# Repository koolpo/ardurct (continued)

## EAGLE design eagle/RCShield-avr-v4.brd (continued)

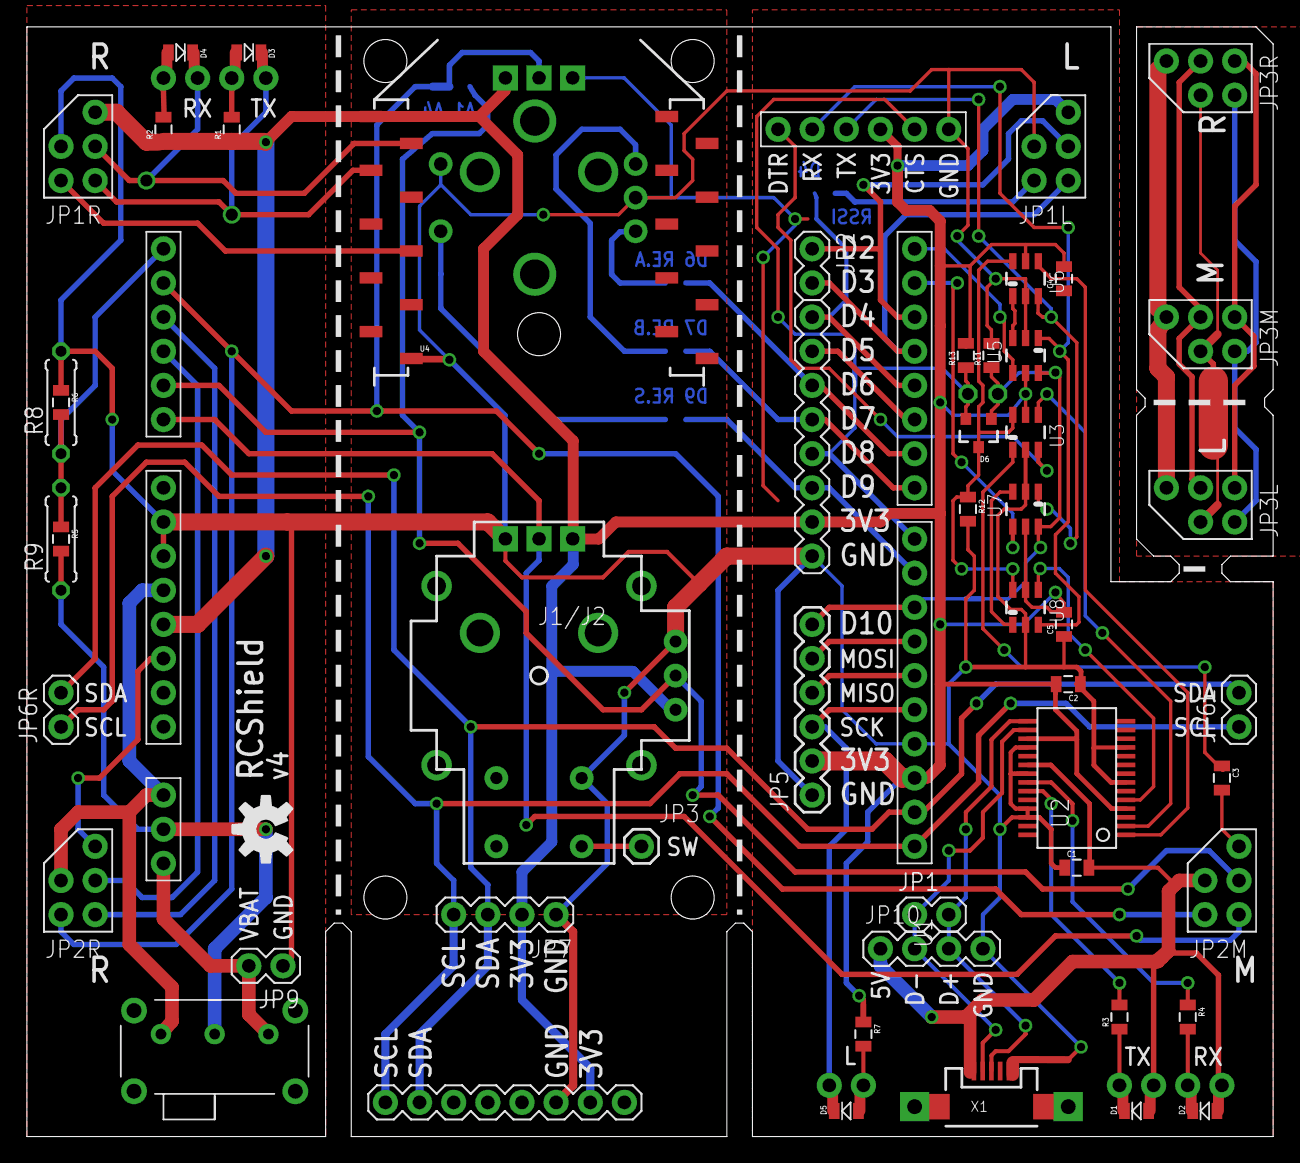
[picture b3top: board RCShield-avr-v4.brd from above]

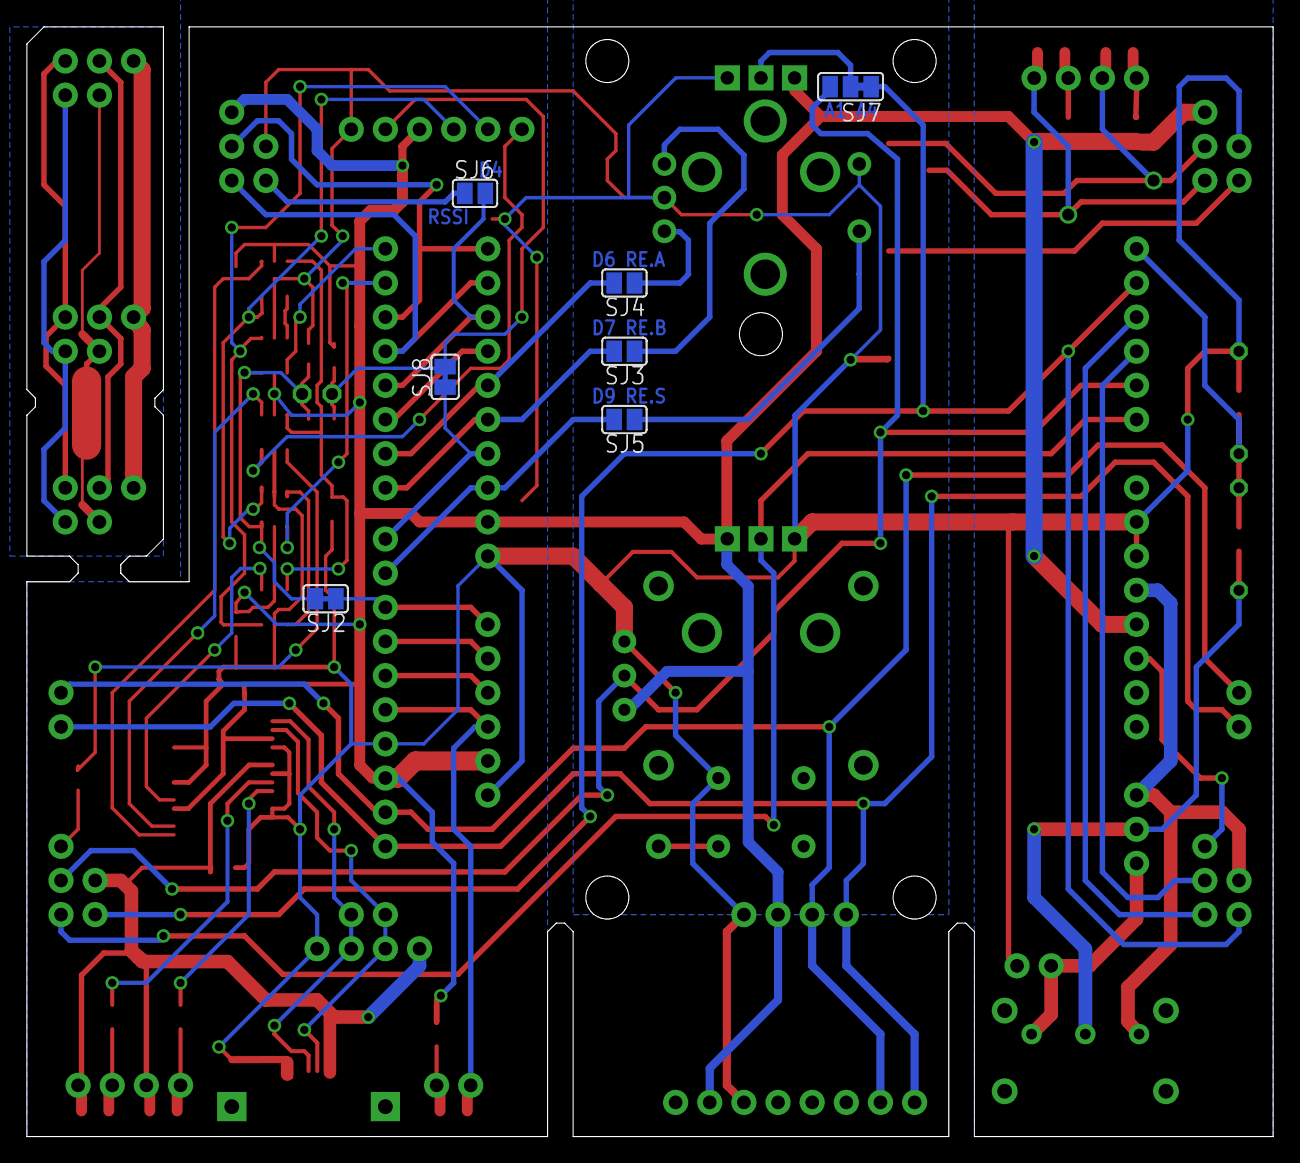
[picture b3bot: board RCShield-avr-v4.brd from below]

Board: 2 copper layers, 92.7 x 82.5 mm, 66 parts (7 on the bottom side), 65 nets.

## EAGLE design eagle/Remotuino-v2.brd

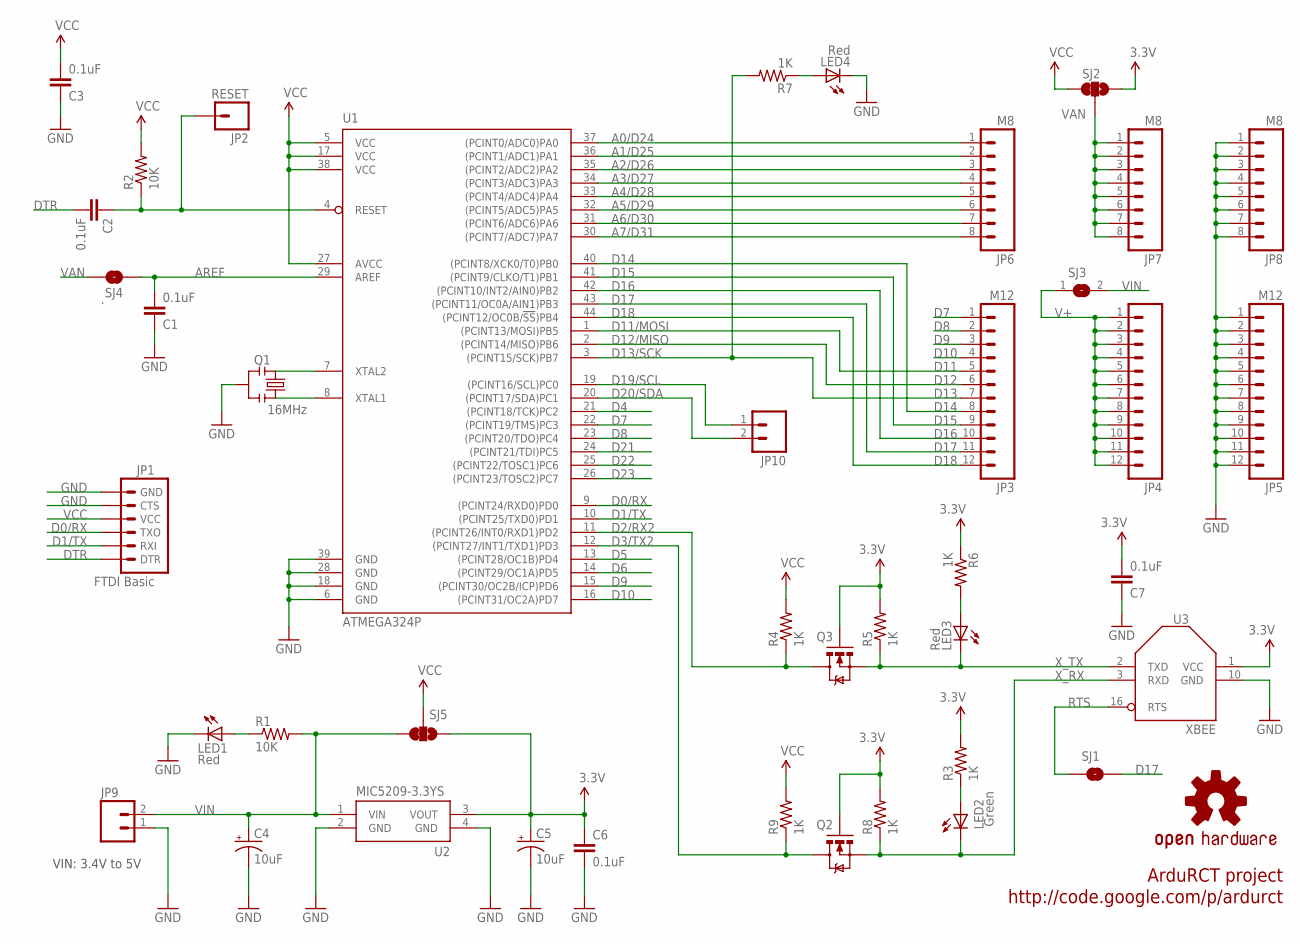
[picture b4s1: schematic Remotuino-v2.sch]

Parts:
C1, C2, C3, C6, C7: 0.1uF; 0805
C4, C5: 10uF; EIA3216
JP1: FTDI Basic; 1X06
JP2: RESET; 1X01
JP3, JP5: M12; 1X12
JP4: M12PTH; 1X12
JP6, JP7, JP8: M8; 1X08
JP9: M02L; 1X2_LONGPAD
JP10: M02; 1X02
LED1, LED3, LED4: Red; LED-0805
LED2: Green; LED-0805
Q1: 16MHz; RESONATOR-SMD
Q2, Q3: BSS138; SOT23-3
R1, R2: 10K; 0805
R3, R4, R5, R6, R7, R8, R9: 1K; 0805
SJ1: SOLDERJUMPERNO; SJ_2S-NO
SJ2, SJ5: SJ_2WAYS_1-2W; SJ_2WAYS_1-2
SJ3: SJ
SJ4: .; SJ_2S-TRACE
U1: ATMEGA324P; TQFP44
U2: MIC5209-3.3YS; SOT223
U3: XBEE; XBEE-MIN
U$2: OSHW-LOGOS; OSHW-LOGO-S

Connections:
3.3V: C5.A (+), C6.1, C7.2, Q2.1 (G), Q3.1 (G), R3.2, R5.2, R6.1, R8.2, SJ2.3, SJ5.3, U2.3 (VOUT), U3.1 (VCC)
A0/D24: JP6.1, U1.37 ((PCINT0/ADC0)PA0)
A1/D25: JP6.2, U1.36 ((PCINT1/ADC1)PA1)
A2/D26: JP6.3, U1.35 ((PCINT2/ADC2)PA2)
A3/D27: JP6.4, U1.34 ((PCINT3/ADC3)PA3)
A4/D28: JP6.5, U1.33 ((PCINT4/ADC4)PA4)
A5/D29: JP6.6, U1.32 ((PCINT5/ADC5)PA5)
A6/D30: JP6.7, U1.31 ((PCINT6/ADC6)PA6)
A7/D31: JP6.8, U1.30 ((PCINT7/ADC7)PA7)
AREF: C1.2, SJ4.2, U1.29 (AREF)
D0/RX: JP1.3 (TXO), U1.9 ((PCINT24/RXD0)PD0)
D1/TX: JP1.2 (RXI), U1.10 ((PCINT25/TXD0)PD1)
D2/RX2: Q3.3 (D), R4.1, U1.11 ((PCINT26/INT0/RXD1)PD2)
D3/TX2: Q2.3 (D), R9.1, U1.12 ((PCINT27/INT1/TXD1)PD3)
D4: U1.21 ((PCINT18/TCK)PC2)
D5: U1.13 ((PCINT28/OC1B)PD4)
D6: U1.14 ((PCINT29/OC1A)PD5)
D7: JP3.1, U1.22 ((PCINT19/TMS)PC3)
D8: JP3.2, U1.23 ((PCINT20/TDO)PC4)
D9: JP3.3, U1.15 ((PCINT30/OC2B/ICP)PD6)
D10: JP3.4, U1.16 ((PCINT31/OC2A)PD7)
D11/MOSI: JP3.5, U1.1 ((PCINT13/MOSI)PB5)
D12/MISO: JP3.6, U1.2 ((PCINT14/MISO)PB6)
D13/SCK: JP3.7, R7.2, U1.3 ((PCINT15/SCK)PB7)
D14: JP3.8, U1.40 ((PCINT8/XCK0/T0)PB0)
D15: JP3.9, U1.41 ((PCINT9/CLKO/T1)PB1)
D16: JP3.10, U1.42 ((PCINT10/INT2/AIN0)PB2)
D17: JP3.11, SJ1.2, U1.43 ((PCINT11/OC0A/AIN1)PB3)
D18: JP3.12, U1.44 ((PCINT12/OC0B/!SS!)PB4)
D19/SCL: JP10.1, U1.19 ((PCINT16/SCL)PC0)
D20/SDA: JP10.2, U1.20 ((PCINT17/SDA)PC1)
D21: U1.24 ((PCINT21/TDI)PC5)
D22: U1.25 ((PCINT22/TOSC1)PC6)
D23: U1.26 ((PCINT23/TOSC2)PC7)
DTR: C2.2, JP1.1 (DTR)
GND: C1.1, C3.1, C4.C (-), C5.C (-), C6.2, C7.1, JP1.5 (CTS), JP1.6 (GND), JP5.1, JP5.2, JP5.3, JP5.4, JP5.5, JP5.6, JP5.7, JP5.8, JP5.9, JP5.10, JP5.11, JP5.12, JP8.1, JP8.2, JP8.3, JP8.4, JP8.5, JP8.6, JP8.7, JP8.8, JP9.1, LED1.2 (C), LED4.2 (C), Q1.2, U1.6 (GND), U1.18 (GND), U1.28 (GND), U1.39 (GND), U2.2 (GND), U2.4 (GND), U3.10 (GND)
unnamed: Q1.1, U1.8 (XTAL1)
unnamed: Q1.3, U1.7 (XTAL2)
unnamed: LED2.1 (A), R3.1
unnamed: LED3.1 (A), R6.2
unnamed: LED4.1 (A), R7.1
unnamed: LED1.1 (A), R1.1
RESET: C2.1, JP2.1, R2.1, U1.4 (RESET)
RTS: SJ1.1, U3.16 (RTS)
V+: JP4.1, JP4.2, JP4.3, JP4.4, JP4.5, JP4.6, JP4.7, JP4.8, JP4.9, JP4.10, JP4.11, JP4.12, SJ3.1
VAN: JP7.1, JP7.2, JP7.3, JP7.4, JP7.5, JP7.6, JP7.7, JP7.8, SJ2.2, SJ4.1
VCC: C3.2, JP1.4 (VCC), R2.2, R4.2, R9.2, SJ2.1, SJ5.2, U1.5 (VCC), U1.17 (VCC), U1.27 (AVCC), U1.38 (VCC)
VIN: C4.A (+), JP9.2, R1.2, SJ3.2, SJ5.1, U2.1 (VIN)
X_RX: LED2.2 (C), Q2.2 (S), R8.1, U3.3 (RXD)
X_TX: LED3.2 (C), Q3.2 (S), R5.1, U3.2 (TXD)

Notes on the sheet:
VIN: 3.4V to 5V
ArduRCT project
http://code.google.com/p/ardurct
D11
D12
D13

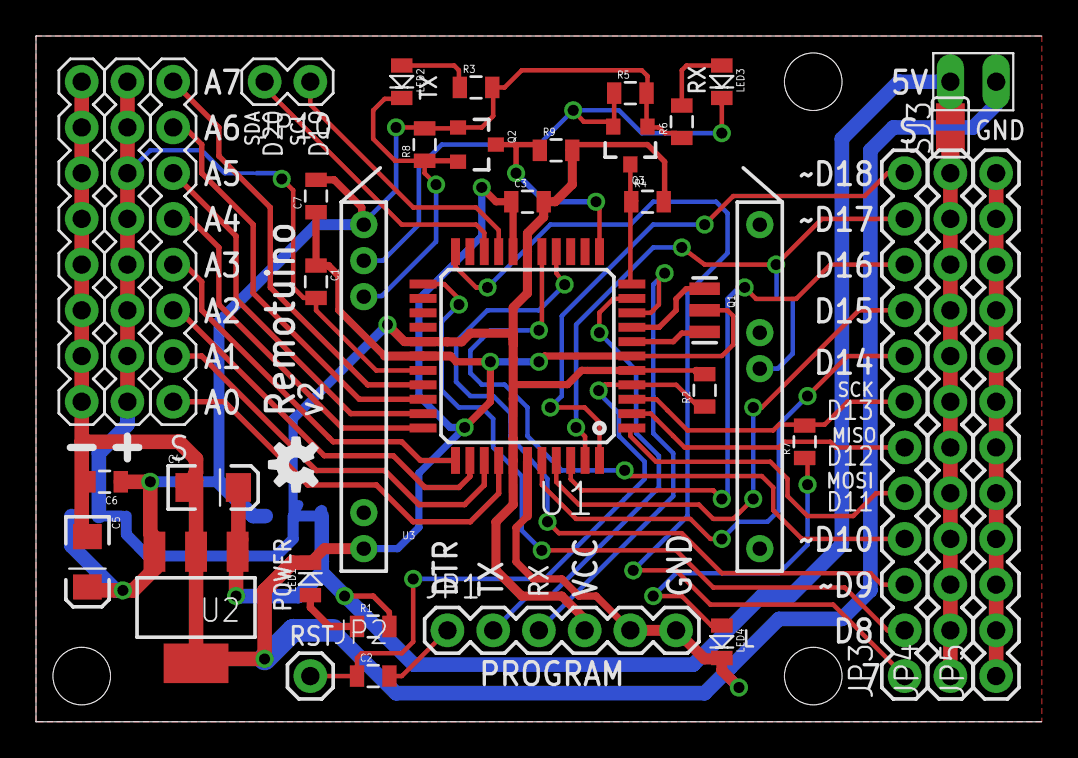
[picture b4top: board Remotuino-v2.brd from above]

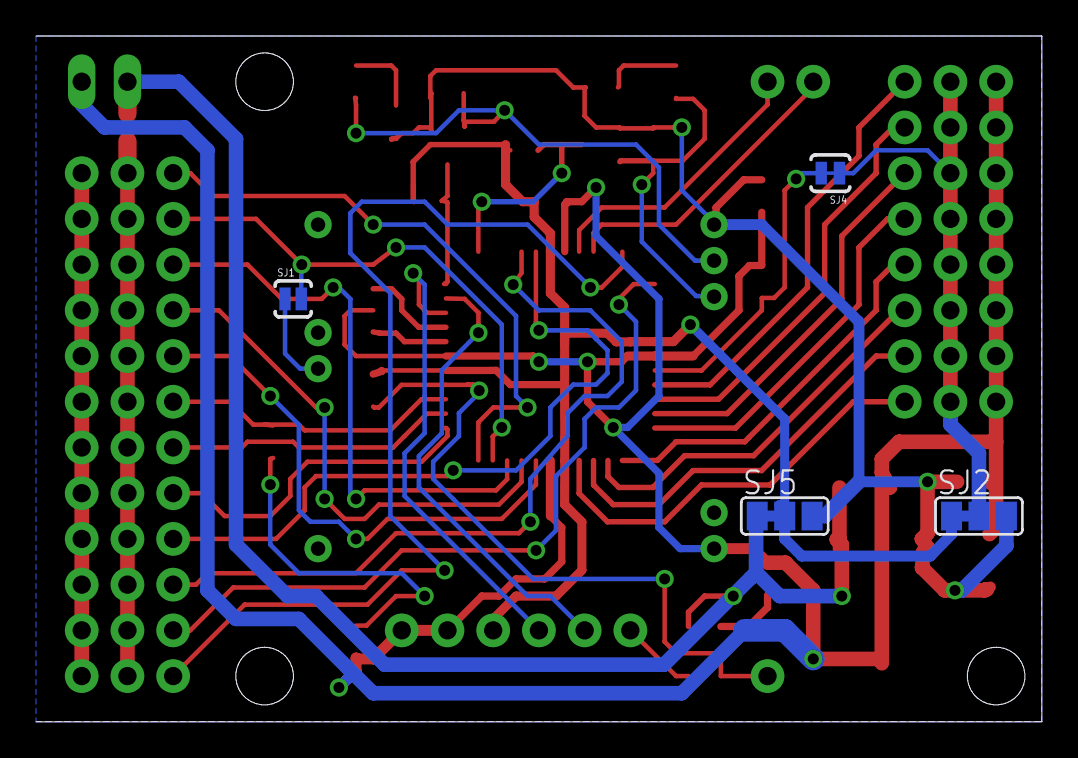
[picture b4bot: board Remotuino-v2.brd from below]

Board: 2 copper layers, 55.9 x 38.1 mm, 42 parts (4 on the bottom side), 44 nets.

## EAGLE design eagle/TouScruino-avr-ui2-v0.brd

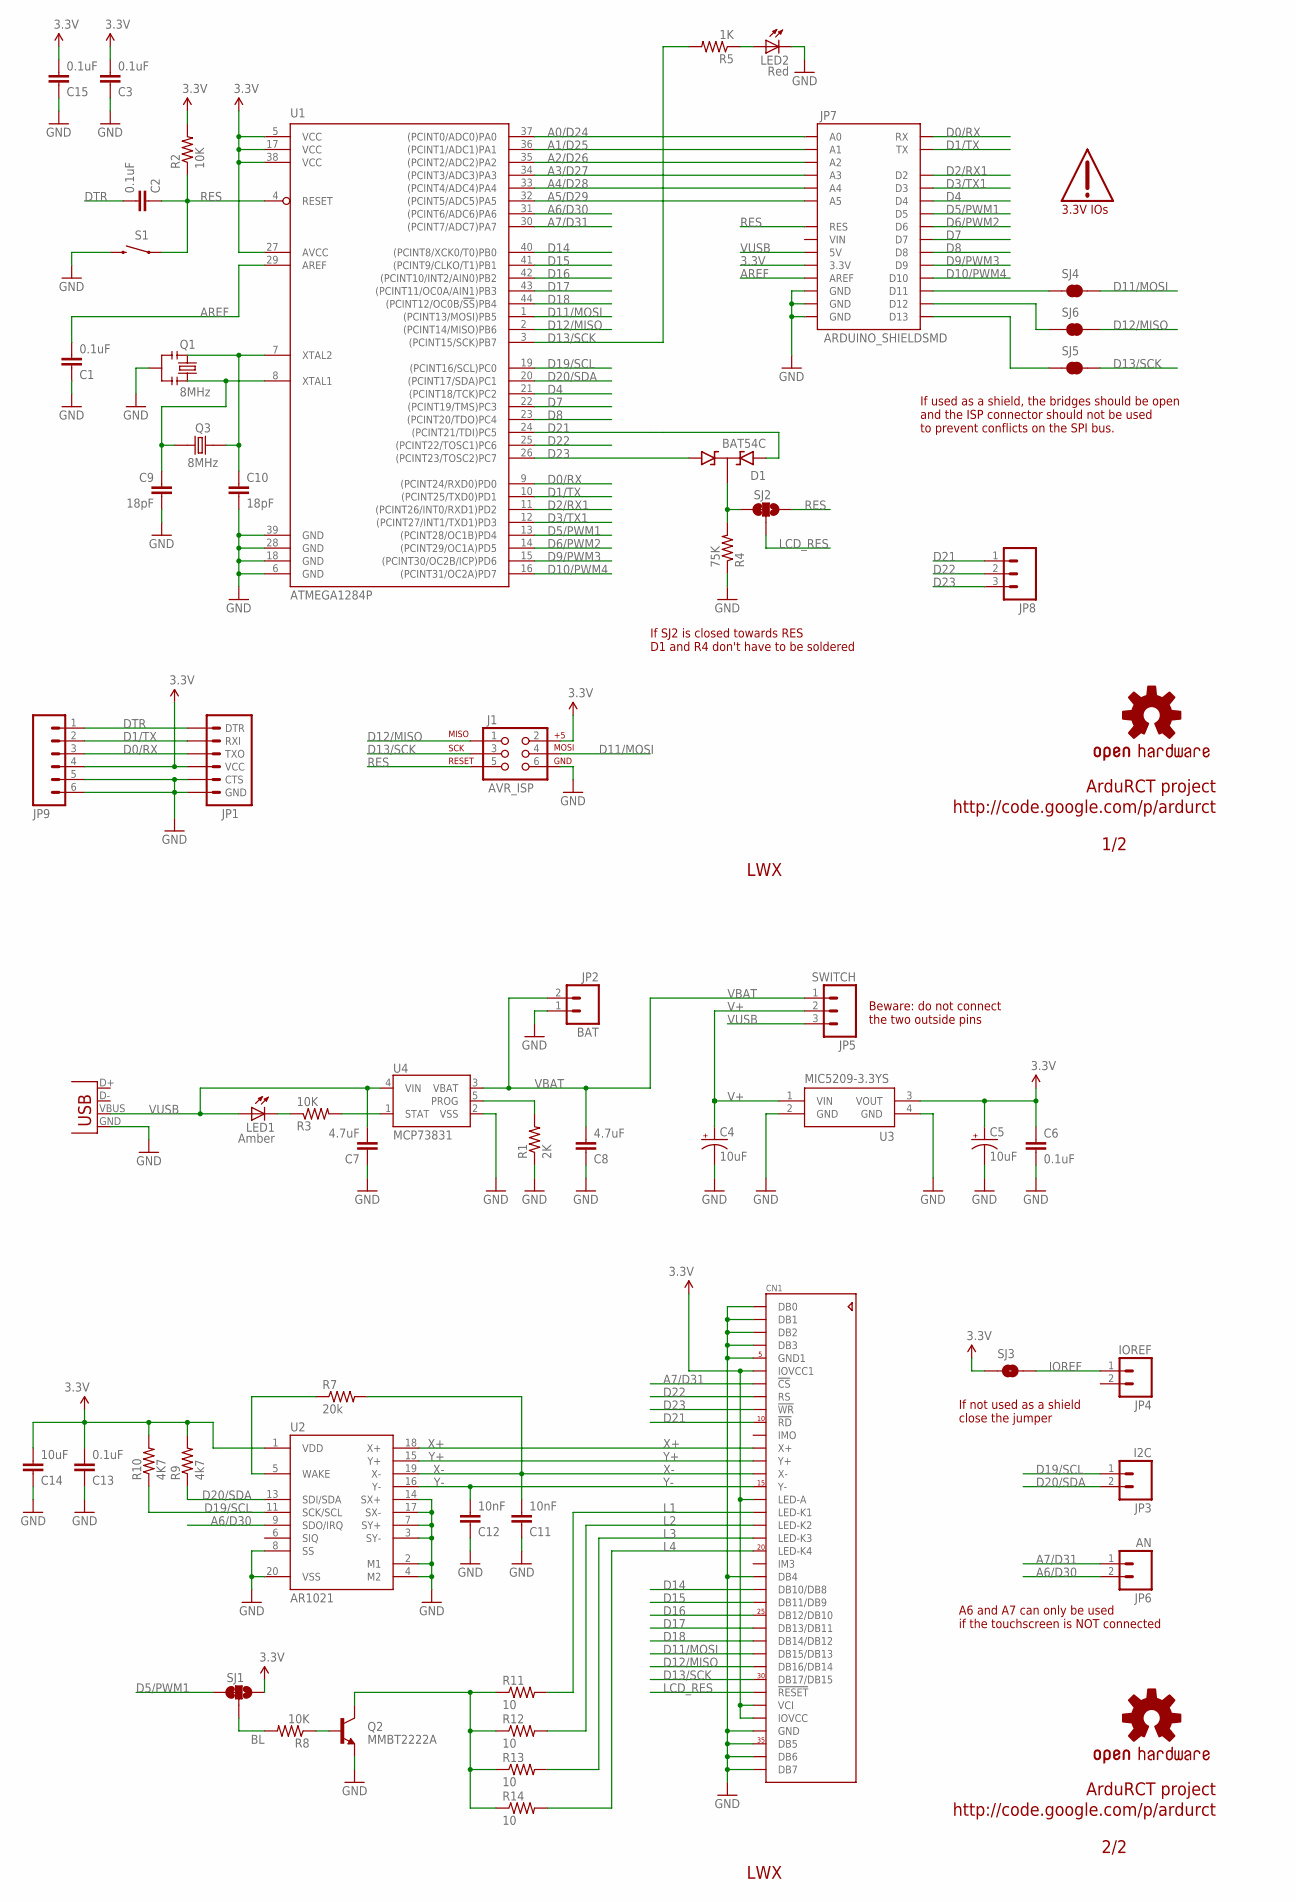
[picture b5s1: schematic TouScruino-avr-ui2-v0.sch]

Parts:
C1, C2, C3, C6, C13, C15: 0.1uF; 0805
C4, C5: 10uF; EIA3216
C7, C8: 4.7uF; 0805
C9, C10: 18pF; 0603-CAP
C11, C12: 10nF; 0805
C14: 10uF; 0805
CN1: ILI9325_LCD1.0MM; ILI9325_28INCH_TS
D1: BAT54C; SOT23-3
J1: AVR_ISP; 2X3
JP1: ARDUINO_SERIAL_PROGRAMPTH; 1X06
JP2: BAT; JST-2-SMD
JP3: I2C; 1X02_SMD
JP4: IOREF; 1X02_SMD
JP5: SWITCH; 1X03_SMD_TH
JP6: AN; 1X02
JP7: ARDUINO_SHIELDSMD; ARDUINO_SHIELD_SMD
JP8: M03PTH; 1X03
JP9: M06SMD; 1X06-SMD
LED1: Amber; LED
LED2: Red; LED
Q1: 8MHz; RESONATOR-SMD
Q2: MMBT2222A; SOT23-3
Q3: 8MHz; CRYSTAL_5X3.2
R1: 2K; 0805
R2, R3, R8: 10K; 0805
R4: 75K; 0805
R5: 1K; 0805
R7: 20k; 0805
R9: 4k7; 0805
R10: 4K7; 0805
R11, R12, R13, R14: 10; 0805
S1: SWITCH-MOMENTARY-2SMD; TACTILE_SWITCH_SMD
SJ1, SJ2: SJ_2WAYS_1-2; SJ_2WAYS_1-2_S
SJ3: SOLDERJUMPERNO; SJ_2S-NO
SJ4, SJ5, SJ6: SOLDERJUMPERTRACE; SJ_2S-TRACE
U1: ATMEGA1284P; TQFP44
U2: AR1021; SSOP20
U3: MIC5209-3.3YS; SOT223
U4: MCP73831; SOT23-5
U$3, U$5: OSHW-LOGOM; OSHW-LOGO-M
U$4: 3.3V_IO
X2: USB; USB-MICROB

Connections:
3.3V: C3.2, C5.A (+), C6.1, C13.2, C14.2, C15.2, CN1.6 (IOVCC1), CN1.16 (LED-A), CN1.32 (VCI), CN1.33 (IOVCC), J1.2, JP1.4 (VCC), JP7.3.3V, JP9.4, R2.2, R9.2, R10.2, SJ1.3, SJ3.1, U1.5 (VCC), U1.17 (VCC), U1.27 (AVCC), U1.38 (VCC), U2.1 (VDD), U3.3 (VOUT)
A0/D24: JP7.A0, U1.37 ((PCINT0/ADC0)PA0)
A1/D25: JP7.A1, U1.36 ((PCINT1/ADC1)PA1)
A2/D26: JP7.A2, U1.35 ((PCINT2/ADC2)PA2)
A3/D27: JP7.A3, U1.34 ((PCINT3/ADC3)PA3)
A4/D28: JP7.A4, U1.33 ((PCINT4/ADC4)PA4)
A5/D29: JP7.A5, U1.32 ((PCINT5/ADC5)PA5)
A6/D30: JP6.2, U1.31 ((PCINT6/ADC6)PA6), U2.9 (SDO/IRQ)
A7/D31: CN1.7 (!CS), JP6.1, U1.30 ((PCINT7/ADC7)PA7)
AREF: C1.2, JP7.AREF, U1.29 (AREF)
BL: R8.2, SJ1.2
D0/RX: JP1.3 (TXO), JP7.RX, JP9.3, U1.9 ((PCINT24/RXD0)PD0)
D1/TX: JP1.2 (RXI), JP7.TX, JP9.2, U1.10 ((PCINT25/TXD0)PD1)
D2/RX1: JP7.D2, U1.11 ((PCINT26/INT0/RXD1)PD2)
D3/TX1: JP7.D3, U1.12 ((PCINT27/INT1/TXD1)PD3)
D4: JP7.D4, U1.21 ((PCINT18/TCK)PC2)
D5/PWM1: JP7.D5, SJ1.1, U1.13 ((PCINT28/OC1B)PD4)
D6/PWM2: JP7.D6, U1.14 ((PCINT29/OC1A)PD5)
D7: JP7.D7, U1.22 ((PCINT19/TMS)PC3)
D8: JP7.D8, U1.23 ((PCINT20/TDO)PC4)
D9/PWM3: JP7.D9, U1.15 ((PCINT30/OC2B/ICP)PD6)
D10/PWM4: JP7.D10, U1.16 ((PCINT31/OC2A)PD7)
D11/MOSI: CN1.28 (DB15/DB13), J1.4, SJ4.2, U1.1 ((PCINT13/MOSI)PB5)
D12/MISO: CN1.29 (DB16/DB14), J1.1, SJ6.2, U1.2 ((PCINT14/MISO)PB6)
D13/SCK: CN1.30 (DB17/DB15), J1.3, R5.2, SJ5.2, U1.3 ((PCINT15/SCK)PB7)
D14: CN1.23 (DB10/DB8), U1.40 ((PCINT8/XCK0/T0)PB0)
D15: CN1.24 (DB11/DB9), U1.41 ((PCINT9/CLKO/T1)PB1)
D16: CN1.25 (DB12/DB10), U1.42 ((PCINT10/INT2/AIN0)PB2)
D17: CN1.26 (DB13/DB11), U1.43 ((PCINT11/OC0A/AIN1)PB3)
D18: CN1.27 (DB14/DB12), U1.44 ((PCINT12/OC0B/!SS!)PB4)
D19/SCL: JP3.1, R10.1, U1.19 ((PCINT16/SCL)PC0), U2.11 (SCK/SCL)
D20/SDA: JP3.2, R9.1, U1.20 ((PCINT17/SDA)PC1), U2.13 (SDI/SDA)
D21: CN1.10 (!RD), D1.2 (A2), JP8.1, U1.24 ((PCINT21/TDI)PC5)
D22: CN1.8 (RS), JP8.2, U1.25 ((PCINT22/TOSC1)PC6)
D23: CN1.9 (!WR), D1.1 (A1), JP8.3, U1.26 ((PCINT23/TOSC2)PC7)
DTR: C2.2, JP1.1 (DTR), JP9.1
GND: C1.1, C3.1, C4.C (-), C5.C (-), C6.2, C7.1, C8.1, C9.2, C10.2, C11.1, C12.1, C13.1, C14.1, C15.1, CN1.1 (DB0), CN1.2 (DB1), CN1.3 (DB2), CN1.4 (DB3), CN1.5 (GND1), CN1.22 (DB4), CN1.34 (GND), CN1.35 (DB5), CN1.36 (DB6), CN1.37 (DB7), J1.6, JP1.5 (CTS), JP1.6 (GND), JP2.1, JP7.GND@0 (GND), JP7.GND@1 (GND), JP7.GND@2 (GND), JP9.5, JP9.6, LED2.C1 (C), Q1.2, Q2.2 (E), R1.1, R4.1, S1.3 (2), U1.6 (GND), U1.18 (GND), U1.28 (GND), U1.39 (GND), U2.2 (M1), U2.3 (SY-), U2.4 (M2), U2.7 (SY+), U2.8 (SS), U2.14 (SX+), U2.17 (SX-), U2.20 (VSS), U3.2 (GND), U3.4 (GND), U4.2 (VSS), X2.GND
IOREF: JP4.1, SJ3.2
L1: CN1.17 (LED-K1), R11.2
L2: CN1.18 (LED-K2), R12.2
L3: CN1.19 (LED-K3), R13.2
L4: CN1.20 (LED-K4), R14.2
LCD_RES: CN1.31 (!RESET), SJ2.2
unnamed: C9.1, Q1.1, Q3.2, U1.8 (XTAL1)
unnamed: C10.1, Q1.3, Q3.1, U1.7 (XTAL2)
unnamed: JP7.D11, SJ4.1
unnamed: Q2.1 (B), R8.1
unnamed: LED2.A1 (A), R5.1
unnamed: R7.1, U2.5 (WAKE)
unnamed: Q2.3 (C), R11.1, R12.1, R13.1, R14.1
unnamed: LED1.C1 (C), R3.1
unnamed: D1.3 (K), R4.2, SJ2.1
unnamed: JP7.D13, SJ5.1
unnamed: R3.2, U4.1 (STAT)
unnamed: R1.2, U4.5 (PROG)
unnamed: JP7.D12, SJ6.1
RES: C2.1, J1.5, JP7.RES, R2.1, S1.1, SJ2.3, U1.4 (RESET)
V+: C4.A (+), JP5.2, U3.1 (VIN)
VBAT: C8.2, JP2.2, JP5.1, U4.3 (VBAT)
VUSB: C7.2, JP5.3, JP7.5V, LED1.A1 (A), U4.4 (VIN), X2.VBUS
X+: CN1.12 (X+), U2.18 (X+)
X-: C11.2, CN1.14 (X-), R7.2, U2.19 (X-)
Y+: CN1.13 (Y+), U2.15 (Y+)
Y-: C12.2, CN1.15 (Y-), U2.16 (Y-)

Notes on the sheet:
LWX
1/2
2/2
Beware: do not connect the two outside pins
If not used as a shield close the jumper
ArduRCT project
http://code.google.com/p/ardurct
If used as a shield, the bridges should be open and the ISP connector should not be used to prevent conflicts on the SPI bus.
A6 and A7 can only be used if the touchscreen is NOT connected
If SJ2 is closed towards RES D1 and R4 don't have to be soldered

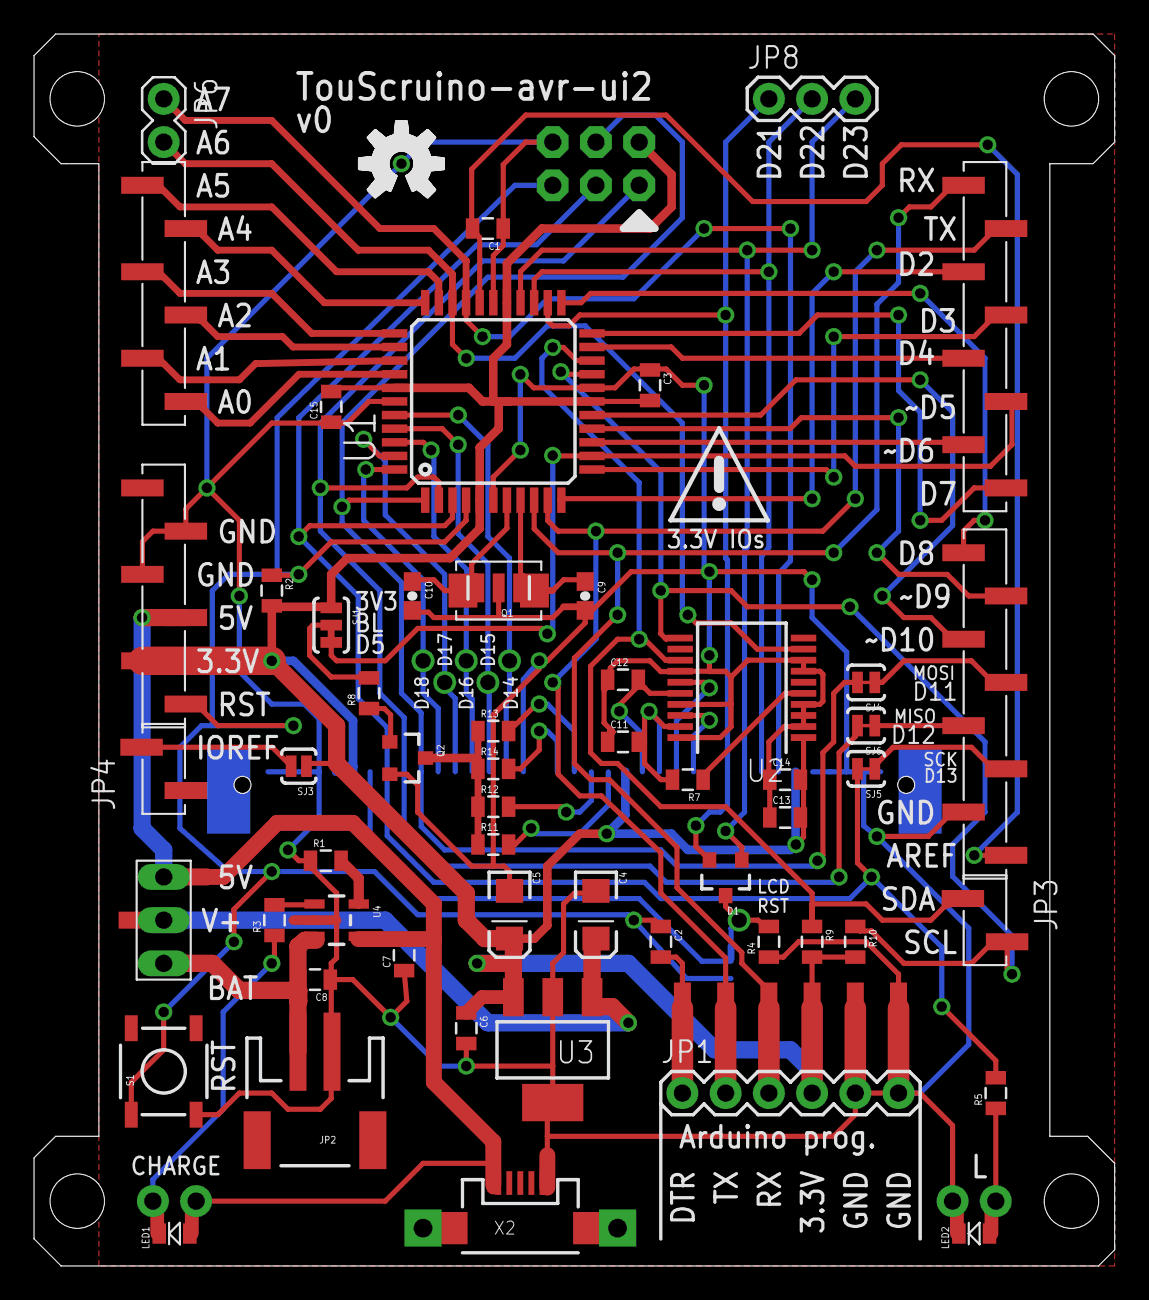
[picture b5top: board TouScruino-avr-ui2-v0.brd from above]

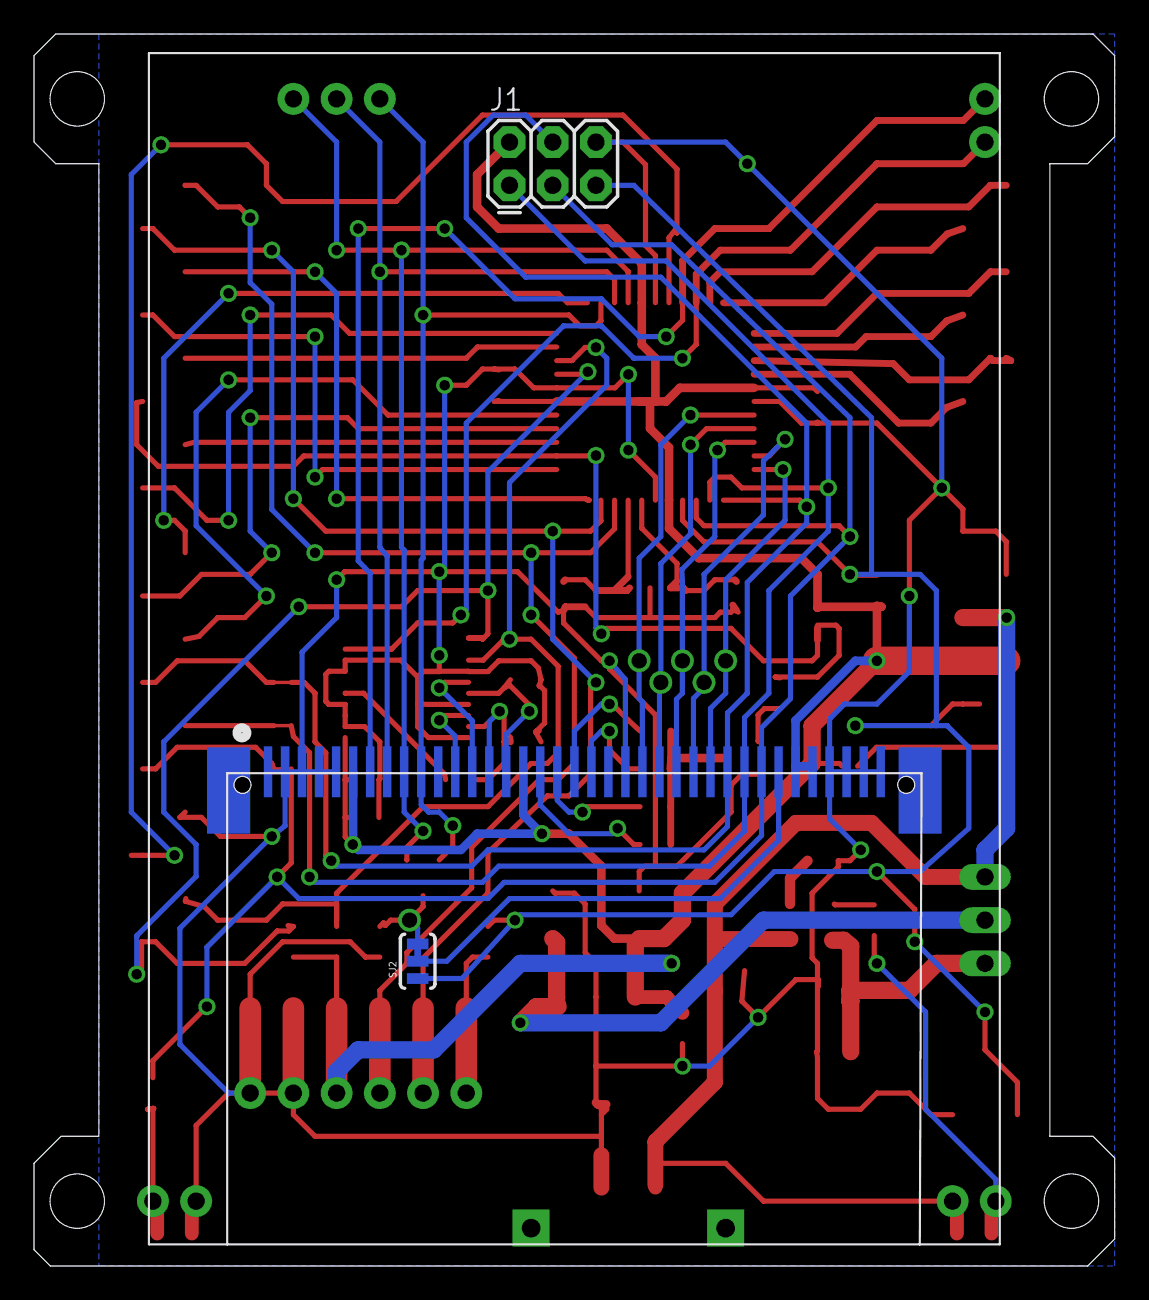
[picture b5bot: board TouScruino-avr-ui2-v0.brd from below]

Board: 2 copper layers, 63.5 x 72.4 mm, 60 parts (4 on the bottom side), 64 nets.

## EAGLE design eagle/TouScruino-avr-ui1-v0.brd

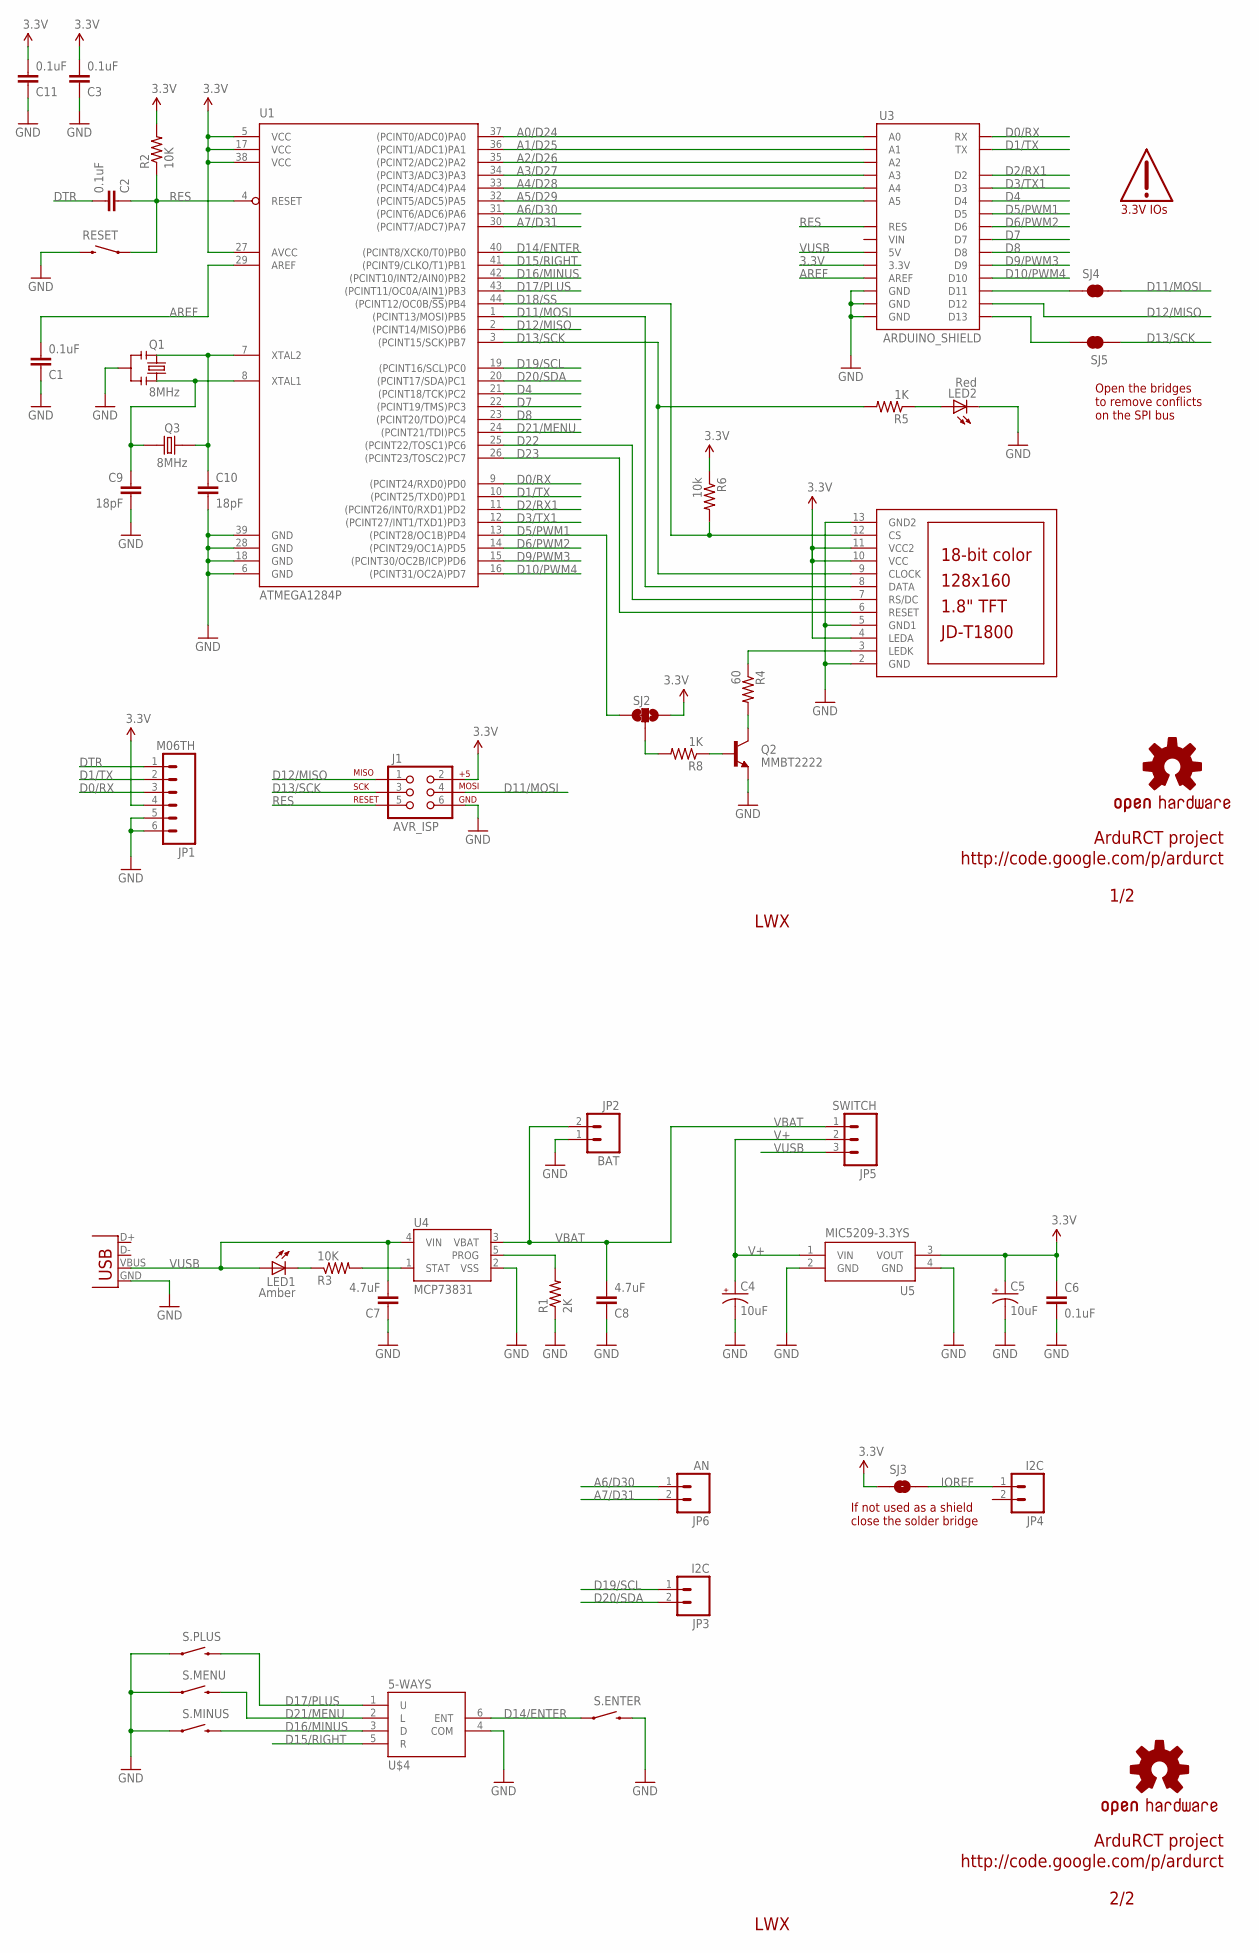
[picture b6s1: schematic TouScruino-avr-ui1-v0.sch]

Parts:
C1, C2, C3, C6, C11: 0.1uF; 0805
C4, C5: 10uF; EIA3216
C7, C8: 4.7uF; 0805
C9, C10: 18pF; 0603-CAP
J1: AVR_ISP; 2X3
JP1: M06TH; 1X06
JP2: BAT; JST-2-SMD
JP3, JP4: I2C; 1X02
JP5: SWITCH; 1X3_LONGPAD
JP6: AN; 1X02
LCD1: JD-T1800
LED1: Amber; LED
LED2: Red; LED
Q1: 8MHz; RESONATOR-SMD
Q2: MMBT2222; SOT23-3
Q3: 8MHz; CRYSTAL_5X3.2
R1: 2K; 0805
R2, R3: 10K; 0805
R4: 60; 0805
R5, R8: 1K; 0805
R6: 10k; 0805
RESET: SWITCH-MOMENTARY-2SMD; TACTILE_SWITCH_SMD
S.ENTER, S.MENU, S.MINUS, S.PLUS: SWITCH_SMD; TACTILE_SWITCH_SMD
SJ2: SJ_2WAYS_1-2; SJ_2WAYS_1-2_S
SJ3: SOLDERJUMPERNO; SJ_2S-NO
SJ4, SJ5: SOLDERJUMPERTRACE; SJ_2S-TRACE
U1: ATMEGA1284P; TQFP44
U3: ARDUINO_SHIELD
U4: MCP73831; SOT23-5
U5: MIC5209-3.3YS; SOT223
U$3, U$5: OSHW-LOGOM; OSHW-LOGO-M
U$4: 5-WAYS; 5-WAYS_ALPS
U$6: 3.3V_IO
X1: USB; USB-MICROB

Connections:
3.3V: C3.2, C5.A (+), C6.1, C11.2, J1.2, JP1.4, LCD1.4 (LEDA), LCD1.10 (VCC), LCD1.11 (VCC2), R2.2, R6.1, SJ2.3, SJ3.1, U1.5 (VCC), U1.17 (VCC), U1.27 (AVCC), U1.38 (VCC), U3.3.3V, U5.3 (VOUT)
A0/D24: U1.37 ((PCINT0/ADC0)PA0), U3.A0
A1/D25: U1.36 ((PCINT1/ADC1)PA1), U3.A1
A2/D26: U1.35 ((PCINT2/ADC2)PA2), U3.A2
A3/D27: U1.34 ((PCINT3/ADC3)PA3), U3.A3
A4/D28: U1.33 ((PCINT4/ADC4)PA4), U3.A4
A5/D29: U1.32 ((PCINT5/ADC5)PA5), U3.A5
A6/D30: JP6.1, U1.31 ((PCINT6/ADC6)PA6)
A7/D31: JP6.2, U1.30 ((PCINT7/ADC7)PA7)
AREF: C1.2, U1.29 (AREF), U3.AREF
BL_CMD: R8.2, SJ2.2
D0/RX: JP1.3, U1.9 ((PCINT24/RXD0)PD0), U3.RX
D1/TX: JP1.2, U1.10 ((PCINT25/TXD0)PD1), U3.TX
D2/RX1: U1.11 ((PCINT26/INT0/RXD1)PD2), U3.D2
D3/TX1: U1.12 ((PCINT27/INT1/TXD1)PD3), U3.D3
D4: U1.21 ((PCINT18/TCK)PC2), U3.D4
D5/PWM1: SJ2.1, U1.13 ((PCINT28/OC1B)PD4), U3.D5
D6/PWM2: U1.14 ((PCINT29/OC1A)PD5), U3.D6
D7: U1.22 ((PCINT19/TMS)PC3), U3.D7
D8: U1.23 ((PCINT20/TDO)PC4), U3.D8
D9/PWM3: U1.15 ((PCINT30/OC2B/ICP)PD6), U3.D9
D10/PWM4: U1.16 ((PCINT31/OC2A)PD7), U3.D10
D11/MOSI: J1.4, LCD1.8 (DATA), SJ4.2, U1.1 ((PCINT13/MOSI)PB5)
D12/MISO: J1.1, U1.2 ((PCINT14/MISO)PB6), U3.D12
D13/SCK: J1.3, LCD1.9 (CLOCK), R5.2, SJ5.1, U1.3 ((PCINT15/SCK)PB7)
D14/ENTER: S.ENTER.1, U1.40 ((PCINT8/XCK0/T0)PB0), U$4.6 (ENT)
D15/RIGHT: U1.41 ((PCINT9/CLKO/T1)PB1), U$4.5 (R)
D16/MINUS: S.MINUS.3 (2), U1.42 ((PCINT10/INT2/AIN0)PB2), U$4.3 (D)
D17/PLUS: S.PLUS.3 (2), U1.43 ((PCINT11/OC0A/AIN1)PB3), U$4.1 (U)
D18/SS: LCD1.12 (CS), R6.2, U1.44 ((PCINT12/OC0B/!SS!)PB4)
D19/SCL: JP3.1, U1.19 ((PCINT16/SCL)PC0)
D20/SDA: JP3.2, U1.20 ((PCINT17/SDA)PC1)
D21/MENU: S.MENU.3 (2), U1.24 ((PCINT21/TDI)PC5), U$4.2 (L)
D22: LCD1.7 (RS/DC), U1.25 ((PCINT22/TOSC1)PC6)
D23: LCD1.6 (RESET), U1.26 ((PCINT23/TOSC2)PC7)
DTR: C2.2, JP1.1
GND: C1.1, C3.1, C4.C (-), C5.C (-), C6.2, C7.1, C8.1, C9.2, C10.2, C11.1, J1.6, JP1.5, JP1.6, JP2.1, LCD1.2 (GND), LCD1.5 (GND1), LCD1.13 (GND2), LED2.C1 (C), Q1.2, Q2.2 (E), R1.1, RESET.3 (2), S.ENTER.3 (2), S.MENU.1, S.MINUS.1, S.PLUS.1, U1.6 (GND), U1.18 (GND), U1.28 (GND), U1.39 (GND), U3.GND@0 (GND), U3.GND@1 (GND), U3.GND@2 (GND), U4.2 (VSS), U5.2 (GND), U5.4 (GND), U$4.4 (COM), X1.GND
IOREF: JP4.1, SJ3.2
unnamed: C9.1, Q1.1, Q3.2, U1.8 (XTAL1)
unnamed: C10.1, Q1.3, Q3.1, U1.7 (XTAL2)
unnamed: LCD1.3 (LEDK), R4.1
unnamed: Q2.1 (B), R8.1
unnamed: LED2.A1 (A), R5.1
unnamed: SJ4.1, U3.D11
unnamed: LED1.C1 (C), R3.1
unnamed: SJ5.2, U3.D13
unnamed: R3.2, U4.1 (STAT)
unnamed: R1.2, U4.5 (PROG)
unnamed: Q2.3 (C), R4.2
RES: C2.1, J1.5, R2.1, RESET.1, U1.4 (RESET), U3.RES
V+: C4.A (+), JP5.2, U5.1 (VIN)
VBAT: C8.2, JP2.2, JP5.1, U4.3 (VBAT)
VUSB: C7.2, JP5.3, LED1.A1 (A), U3.5V, U4.4 (VIN), X1.VBUS

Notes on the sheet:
LWX
1/2
2/2
If not used as a shield close the solder bridge
ArduRCT project
http://code.google.com/p/ardurct
Open the bridges to remove conflicts on the SPI bus
